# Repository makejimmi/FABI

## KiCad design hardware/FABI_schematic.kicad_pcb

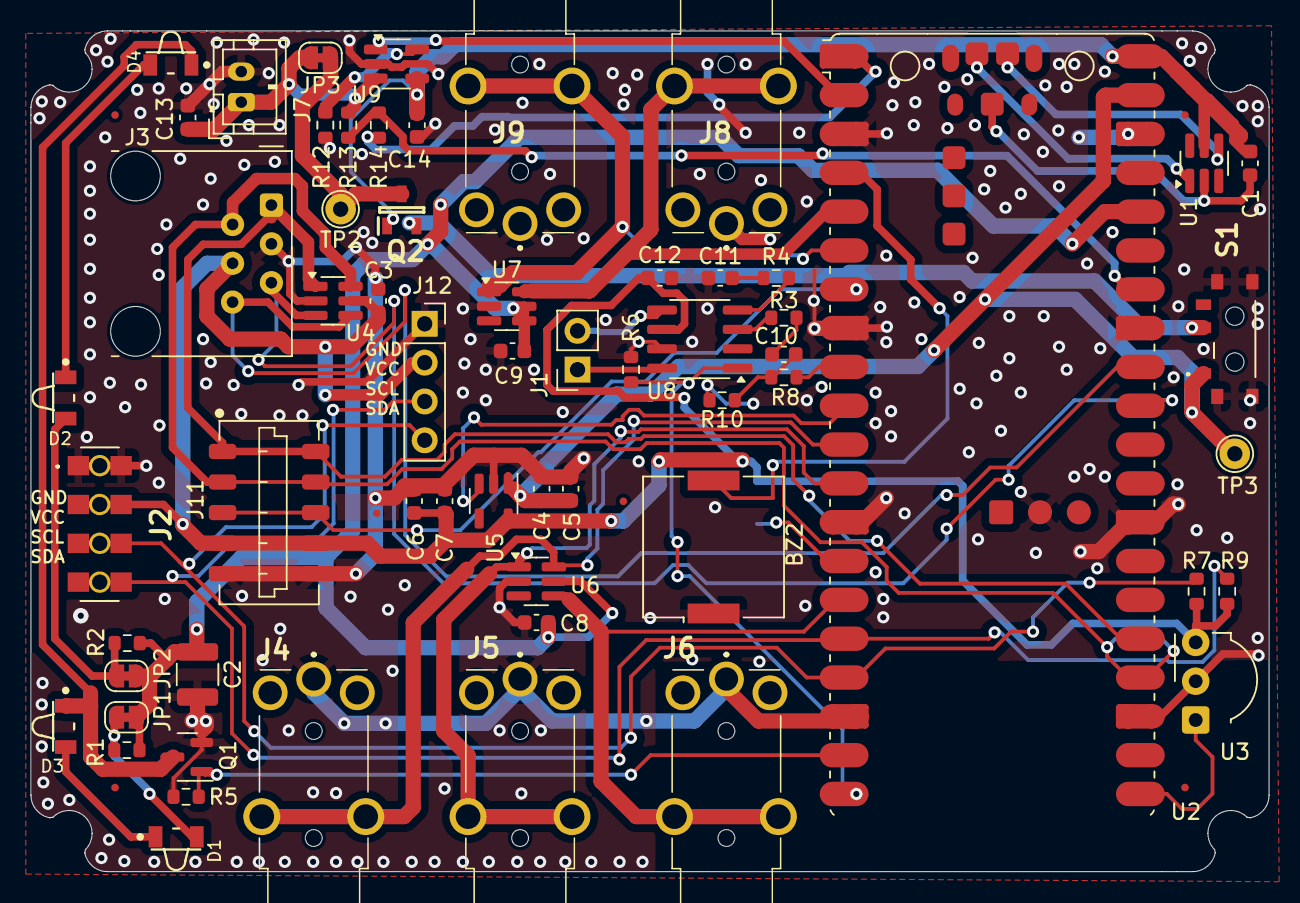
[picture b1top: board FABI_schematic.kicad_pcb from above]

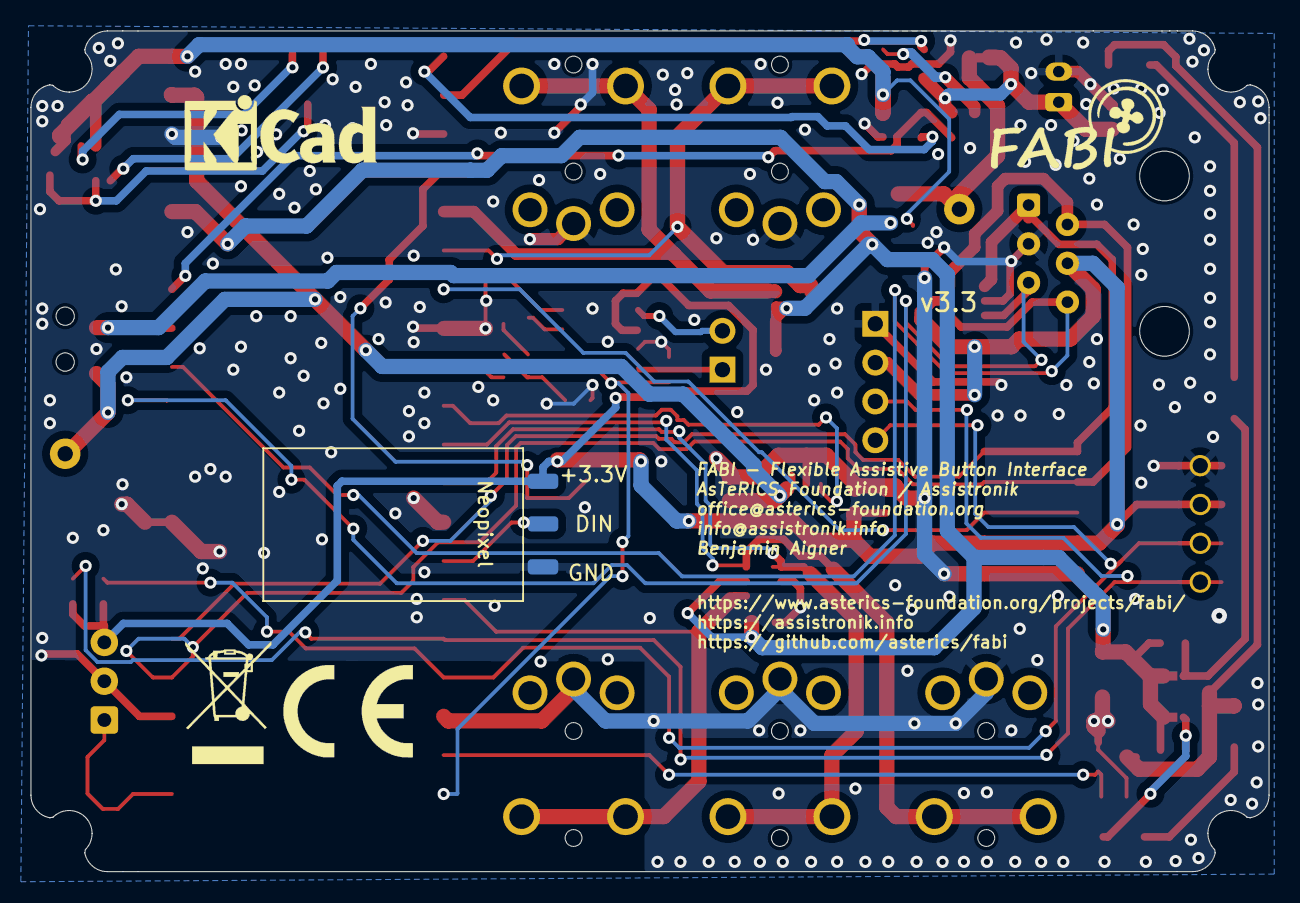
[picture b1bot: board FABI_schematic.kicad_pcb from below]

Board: 2 copper layers, 81.0 x 55.0 mm, 73 parts (7 on the bottom side), 46 nets.

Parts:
BZ2: PKMCS0909E4000; Buzzer_Murata_PKMCS0909E
C1, C3, C5, C6, C8, C9: 100n; C_0603_1608Metric
C2: 100uF/6.3V; C_1210_3225Metric
C4, C7: 1uF / >6.3V / X7R; C_0603_1608Metric
C10, C11: 1u; C_0603_1608Metric
C12: 10u; C_0603_1608Metric
C13, C14: 4.7u; C_0603_1608Metric
D1, D2, D3, D4: SFH4045; SFH4045N
FID1, FID2, FID3, FID4, FID5, FID6: Fiducial; Fiducial_0.5mm_Mask1mm
J1: Conn_01x02_Pin; PinSocket_1x02_P2.54mm_Vertical
J2: display_connector_91601-304LF; 91601304LF
J3: 54601-906WPLF; RJ12_Amphenol_54601-x06_Horizontal
J4, J5, J6, J8, J9: 54-00174 / FC68125; FC68125
J7: JST PH2P ST; JST_PH_B2B-PH-K_1x02_P2.00mm_Vertical
J11: 009159005551906
J11_GND1, J11_VDD1, J11_data1: Conn_01x01_Male; SolderWirePad_1x01_SMD_1x2mm_NOPASTE
J12: Conn_01x04_Socket; PinSocket_1x04_P2.54mm_Vertical
JP1, JP2, JP3: SolderJumper_2_Bridged; SolderJumper-2_P1.3mm_Bridged_RoundedPad1.0x1.5mm
LOGO1: Logo_FABI; FABI_Logo_s
LOGO2: Logo_KiCAD; KiCad-Logo_5mm_SilkScreen
LOGO3: Logo_CE; CE-Logo_8.5x6mm_SilkScreen
LOGO4: Logo_WEEE; WEEE-Logo_5.6x8mm_SilkScreen
Q1: BSS806; SOT-23
Q2: DMG2305UXQ-7; SOT96P240X110-3N
R1, R2: DNP; R_0603_1608Metric
R3, R4: 100; R_0603_1608Metric
R5, R6, R7, R9: 4k7; R_0603_1608Metric
R8, R10: 10k; R_0603_1608Metric
R12: 3k3; R_0603_1608Metric
R13, R14: 100k; R_0603_1608Metric
S1: 450404015514
TP2, TP3: TestPoint_Probe; TestPoint_THTPad_D2.0mm_Drill1.0mm
U1: D5V0F4U6SO; SC-74-6_1.55x2.9mm_P0.95mm
U2: Pico 2W; RaspberryPi_Pico_W_SMD
U3: TSOP4838; Vishay_MOLD-3Pin
U4, U6, U7: D1213A-04SO-7; SC-74-6_1.55x2.9mm_P0.95mm
U5: MIC5504-3.3YM5; SOT-23-5
U8: PAM8302AAS; SOIC-8_3.9x4.9mm_P1.27mm
U9: MCP73831-2; SOT-23-5_HandSoldering

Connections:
+3.3VADC: C3.1, C6.1, C7.1, C12.2, J2.3, J3.4, J11.4, J11_VDD1.1, J12.2, R7.2, R9.2, U3.3 (Vs), U4.5 (VBUS), U5.5 (VOUT), U8.6 (VDD)
/3V3_ADC_ENABLE: U2.10 (GPIO7), U5.3 (EN)
/Audio_SD: R6.2, U2.20 (GPIO15), U8.1 (~SD)
/Audio_Signal: R8.1, U2.9 (GPIO6)
/BUTTON1: J4.3T, U2.11 (GPIO8), U6.6 (I/O4)
/BUTTON2: J5.3T, U2.12 (GPIO9), U6.1 (I/O1)
/BUTTON3: J6.3T, U2.15 (GPIO11), U6.4 (I/O3)
/BUTTON4: J8.3T, U2.5 (GPIO3), U7.6 (I/O4)
/BUTTON5: J9.3T, U2.6 (GPIO4), U7.1 (I/O1)
/BUZZER: BZ2.2 (+), U2.4 (GPIO2)
/CHARGE_STAT: U2.2 (GPIO1), U9.1 (STAT)
/EXT1: J3.5, U2.31 (GPIO26_ADC0), U4.3 (I/O2)
/EXT2: J3.6, U2.32 (GPIO27_ADC1), U4.4 (I/O3)
/IR_LED: Q1.1 (G), R5.2, U2.19 (GPIO14)
/IR_TSOP: U2.21 (GPIO16), U3.1 (OUT)
/MPRLS_DRDY_RES: J11.3, U2.7 (GPIO5)
/NEOPIXEL: J11_data1.1, U2.14 (GPIO10)
/SCL: J3.1, J11.1, U2.25 (GPIO19), U4.1 (I/O1)
/SCL_INT: J2.5, J12.4, R7.1, U2.17 (GPIO13)
/SDA: J3.2, J11.2, U2.24 (GPIO18), U4.6 (I/O4)
/SDA_INT: J2.7, J12.3, R9.1, U2.16 (GPIO12)
/V_BATT_MEASURE: R13.2, R14.1, U2.34 (GPIO28_ADC2)
/V_BATT_VD_SWITCH: R14.2, U2.1 (GPIO0)
GND: BZ2.1 (-), C2.2, C3.2, C4.2, C5.2, C6.2, C7.2, C8.2, C9.2, C11.1, C12.1, C13.2, C14.2, J2.1, J3.3, J4.1S, J5.1S, J6.1S, J7.2, J8.1S, J9.1S, J11.5, J11_GND1.1, J12.1, Q1.2 (S), R5.1, R6.1, R10.2, R12.2, S1.MP1, S1.MP2, S1.MP3, S1.MP4, U2.3 (GND), U2.8 (GND), U2.13 (GND), U2.18 (GND), U2.23 (GND), U2.28 (GND), U2.33 (AGND), U2.38 (GND), U2.D2 (GND), U3.2 (GND), U4.2 (GND), U5.2 (GND), U6.2 (GND), U7.2 (GND), U8.7 (GND), U9.2 (V_{SS})
unnamed: C10.1, R8.2, R10.1
unnamed: C10.2, R3.2
unnamed: C11.2, R4.2
unnamed: D1.2 (A), JP1.2 (B), R1.1
unnamed: D1.1 (K), D3.2 (A)
unnamed: D2.2 (A), JP2.2 (B), R2.1
unnamed: D2.1 (K), D4.2 (A)
unnamed: D3.1 (K), D4.1 (K), Q1.3 (D)
unnamed: J1.1, U8.8 (OUT-)
unnamed: J1.2, U8.5 (OUT+)
unnamed: JP3.1 (A), Q2.3 (D), TP2.1
unnamed: C1.2, U1.2 (GND), U2.TP1 (USB_GND)
unnamed: U1.1 (I/O1), U2.TP3 (USB_DP)
unnamed: U1.4 (I/O3), U2.TP2 (USB_DM)
unnamed: R3.1, U8.3 (IN+)
unnamed: R4.1, U8.4 (IN-)
unnamed: R12.1, U9.5 (PROG)
VBUS: C1.1, C14.1, Q2.1 (G), U1.5 (VBUS), U2.40 (VBUS), U9.4 (V_{DD})
VCC: C2.1, C8.1, C9.1, JP1.1 (A), JP2.1 (A), R1.2, R2.2, U2.36 (3V3), U6.5 (VBUS), U7.4 (I/O3), U7.5 (VBUS)
VSYS: C4.1, C5.1, S1.1, TP3.1, U2.39 (VSYS), U5.1 (VIN)
V_BATT: C13.1, J7.1, JP3.2 (B), R13.1, U9.3 (V_{BAT})
V_PWR_SWITCH: Q2.2 (S), S1.2

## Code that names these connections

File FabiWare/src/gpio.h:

/*
     FLipWare - AsTeRICS Foundation
     For more info please visit: https://www.asterics-foundation.org

     Module: gpio.h - functions for leds and buttons

   This program is distributed in the hope that it will be useful,
   but WITHOUT ANY WARRANTY; See the GNU General Public License:
   http://www.gnu.org/licenses/gpl-3.0.en.html

*/

#ifndef _GPIO_H_
#define _GPIO_H_

#include <Arduino.h>

/**
   constant definitions for pin assignments
*/

// device-specific settings and pin locations 
#ifdef FLIPMOUSE
  #define NUMBER_OF_PHYSICAL_BUTTONS 3      // number of physical buttons for FlipMouse
  #define PHYSICAL_BUTTON_MAP {17, 28, 20}  // gpio pin assignment for buttons
  #define NEOPIXEL_PIN   15   // physical pin for neopixel LED
  #define TONE_PIN       25   // physical pin for piezo buzzer
  #define IR_LED_PIN     19   //  IR-Led output pin for FlipMouse
  #define DRDY_PIN       21   // Data ready pin of NAU chip for FlipMouse
  #define ANALOG_PRESSURE_SENSOR_PIN A3   // input pin if an analog pressure sensor is used with FlipMouse3 PCB 
#else 
  #define NUMBER_OF_PHYSICAL_BUTTONS 5      // number of physical switches for FABI/FlipPad
  #define PHYSICAL_BUTTON_MAP {11,9,8,4,3}
  #define NEOPIXEL_PIN   10
  #define TONE_PIN        2    
  #define IR_LED_PIN     14
  #define DRDY_PIN       27    // Data ready pin of NAU chip (FABI EXT connector, EXT2 pin)
  #define ANALOG_PRESSURE_SENSOR_PIN A0   // input pin if an analog pressure sensor is used with FABI3 PCB
          // note that A0 is also used by an analog x/y sensor, so both can't be used at the same time

  // pins for battery management system for FABI 
  #define V_BATT_VD_SWITCH_PIN 0    // GPIO pin controlling the voltage divider for battery measurement
  #define V_BATT_MEASURE_PIN  A2    // ADC pin for measuring battery voltage
  #define CHARGE_STAT_PIN      1    // pin connected to the charging status output

  // remap pins for I2C interfaces for FABI / FlipPad
  #define PIN_WIRE0_SDA_ 12
  #define PIN_WIRE0_SCL_ 13
  #define PIN_WIRE1_SDA_ 18
  #define PIN_WIRE1_SCL_ 19

  #define AUDIO_SIGNAL_PIN    6   // PWM audio signal pin
  #define AUDIO_AMP_SD_PIN   15   // PAM audio amp shutdown pin (active low)
#endif


// common pin locations
#define IR_SENSOR_PIN   16   //  input pin of the TSOP IR receiver
#define LDO_ENABLE_PIN   7   // Enable pin for the MIC5504 3,3V regulator (VCC supply for sensors)
#define ANALOG_FORCE_SENSOR_X_PIN A0   // input pin if an analog force sensor is used (x axis) 
#define ANALOG_FORCE_SENSOR_Y_PIN A1   // input pin if an analog force sensor is used (y axis) 


/**
   extern declaration of static variables
   which shall be accessed from other modules
*/
extern int8_t  input_map[NUMBER_OF_PHYSICAL_BUTTONS];  // maps the button number to physical pin

/**
   @name initGPIO
   @brief initializes data direction of gpio pins
   @return none
*/
void initGPIO();

/**
   @name initBlink
   @brief initializes an LED blinking sequence
   @return none
*/
void initBlink(uint8_t count, uint8_t startTime);


/**
   @name updateLeds
   @brief update leds according to current slot number / blinking actions
   @return none
*/
void updateLeds();

/**
   @name setLeds
   @brief set the LEDs (or the Neopixel directly)
   @return none
   @param LEDs (bits 0-3; Neopixel equals bit 0 R; bit 1 G; bit 2 B)
   @note Only used in CIM mode.
*/
void setLeds(uint8_t leds);

/**
   @name clearLeds
   @brief clears the LEDs
   @return none
*/
void clearLeds();

#endif

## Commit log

2024-11-14 First Version BMS; Redundant Components removed; Rewired VCC components as preparation for low power design
2024-11-18 Moved U4 Component needed for External Sensor in order to gain more space
2024-11-18 Added all prev. modifications to SRC_v3.0 update by ChrisVeigl; Removed redundant LDO; Most components of the BMS is on the board except for testpoints and battery measurement resistors; Wired most c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
2024-11-18 Ran DRC and fixued some warnings
2024-11-19 Moved S-Diode over to PWR_Switch (far right); Rewired all the added components; Moved R7 & R9 so TP3 + PWR_Switch + S-Diode would have space; Made space for TP2 & TP4 and wired them accordingly; Ran 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
2024-11-20 Ran DRC again and fixed the issues of yesterday's (19.11.24) commit, the issues lied in two ground islands on the B.Cu that were not connected; Rereouted BUTTON4 route in the area of J8 and the NET-(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
2024-11-22 Added missing sheet which caused problems for collaborators when trying to open the schematic
2024-11-29 Added solder jumper between BAT and p-MOS; Rewired battery level measurem. to GPIO pin in order to have it off when not needed; Changed all Rs into EU Rs; Renamed all components for them to be unifor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
2024-11-30 Done more finetuning; No more ADC Pin on the Pico W left, waiting for response/recommendation of prof.; Made sure that every route is correct; Added new GPIO inputs, namely voltage divider so it woul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
2024-11-30 Checked for correct wiring of new conductor tracks (new, in the scope of this project); Layout improved;
2024-12-02 Changed pins for J3 connector as it's sufficient to have I2C1 (GP18, GP19) for SDA/SCL, does not need ADC; V_BATT_MEASURE now uses GP28 with the built-in ADC; Connector J12 now uses 3.3V as well (fro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
2024-12-04 Removed PWR_FLAGS except for VSYS; Removed NT2 (obsolete); Updated Schematics PDF; Reduced V_PWR_SWITCH routes to 1 from 2 to make space for VCC due to it being routed around the mounting holes of co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
2024-12-04 Moved FABI Logo; Changed some names; Changed VSYS label on LPW1; Updated SCH PDF;
2025-01-03 Changed some labels and added minor details
2025-01-03 Added sheet comments
2025-01-15 removed short between Mosfet G/S, some other minor changes
2025-01-17 Added battery management functions & inactivity management & power sleep (lpwFuncs); New pins defined (lpwFuncs); Added new variables to sensorData struct (FlipWare.h); Added battery display (display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
2025-01-17 Added battery management, inactivity management and new pin definitions (lpwFuncs); Added new variables to SensorData struct (FlipWare.h); Modified displayUpdate() to constitute battery (display.cpp)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
2025-01-18 Readded lpwFuncs.h
2025-01-18 Added Battery Bed + Hole for Power Switch
2025-01-18 Adjusted routing to improve ground/copper area coverage; Added 3D models
2025-01-20 Moved all 3rd party files into a separate folder powermanagement; Improved reliability of battery read;
2025-04-06 Resetted to prior to commit 61a2890 (FW change) and readded HW changes/commits:
    Added Battery Bed + Hole for Power Switch
    Adjusted routing to improve ground/copper area coverage
    Added 3D Models (54601-906WPLFc.stp, PKMCS0909E4000-R1--3DModel-STEP-56544.STEP)
2025-04-06 Modified screw holes from bot case (affected PCB when trying to assemble case) to the same x, y positions as the top case design
2025-05-21 Changed dormant interrupt source from one wake up pin to all pins specified by input_map[]
    Added pull ups to dormant interrupt pins to tackle occasional and unwanted wake ups
2025-05-21 Setup that consistently gets down to ~700 uA in DORMANT
2025-05-21 Added function 'initDormant'; gets dormant mode power consumption down to ~4.5mA; sometimes drops down to ~700uA, why?
    -> refer to Setup in new temporary branch 'fm-fabi' in Fork
2025-05-21 Added other setups in which the dormant mode was tested, for more info refer to code (measurements also available in code)
    Usage: Copy code into src/main.cpp, flash
    Note: BUILTIN-LED will blink in normal operation and turn off in DORMANT
2025-05-22 Added 'goingDormant' flag to address conflict with periodic I2C device checks; current in DORMANT: ~700 uA now
    potential reason: interrupted i2c transaction during sleep transition? the likelihood is very low for that to happen
